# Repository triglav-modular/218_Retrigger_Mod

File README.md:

# 218r Retrigger Mod

This is a small add-on PCB that allows for new triggers to be sent from the 218r on each consecutive note without lifting a finger.  It converts the changes in the v/oct output into triggers and adds them to the pulse output. 

There's no need to change any components on the 218r. The "key" and "pulse" inputs just go to the pads above their respective banana jacks. "out" goes directly to the pulse out bananas.
Use a bolt standoff to install it above the STM32.

https://user-images.githubusercontent.com/3920717/165109417-bb7ef8a8-ca0e-416d-88e8-91f72d75c058.mp4

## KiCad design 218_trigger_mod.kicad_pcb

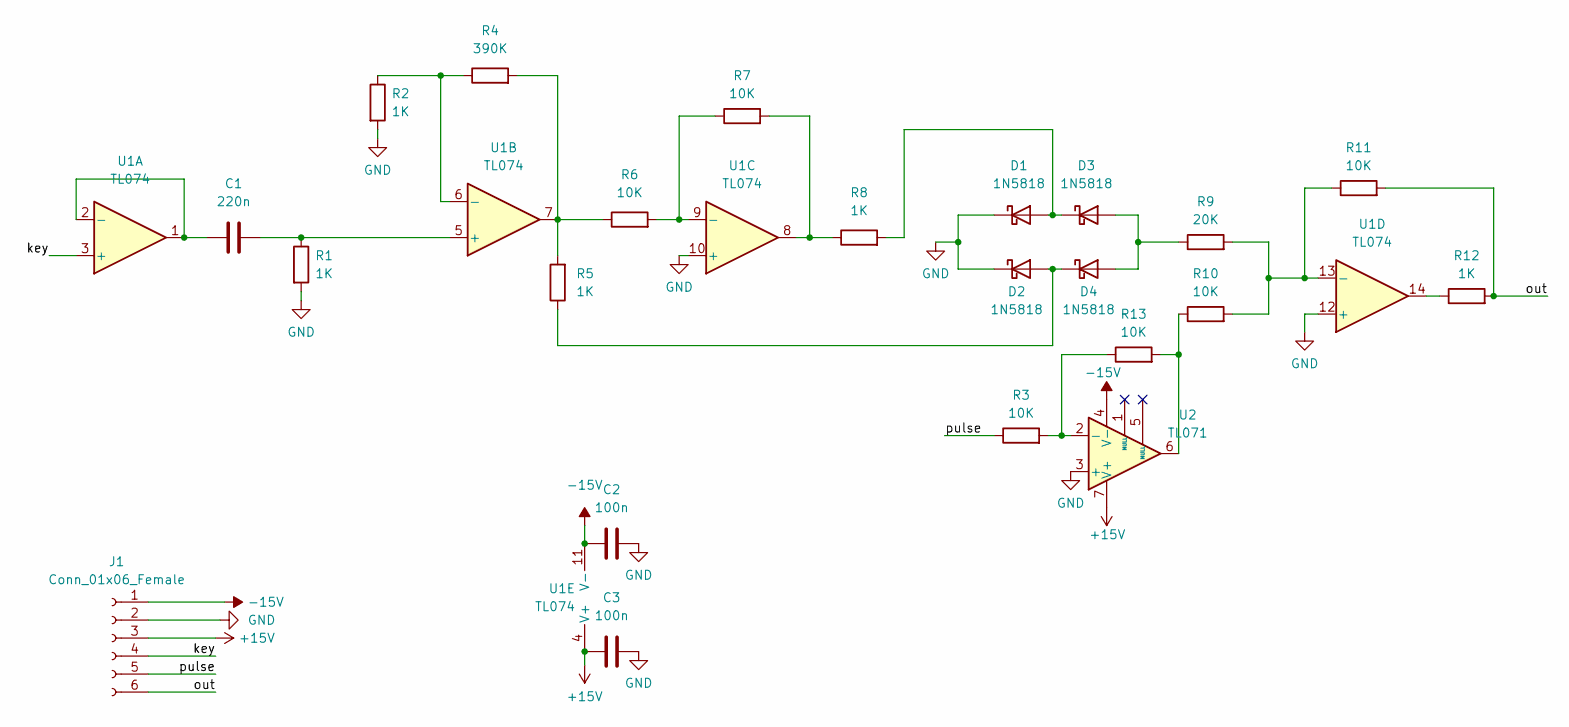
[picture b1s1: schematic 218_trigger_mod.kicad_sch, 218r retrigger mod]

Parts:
C1: 220n; C_Rect_L7.0mm_W3.5mm_P5.00mm
C2, C3: 100n; C_Rect_L7.0mm_W3.5mm_P5.00mm
D1, D2, D3, D4: 1N5818; D_DO-41_SOD81_P7.62mm_Horizontal
J1: Conn_01x06_Female; PinHeader_1x06_P2.54mm_Vertical
R1, R2, R5, R8, R12: 1K; MusicThingModular-10MM_RESISTOR
R3, R6, R7, R10, R11, R13: 10K; MusicThingModular-10MM_RESISTOR
R4: 390K; MusicThingModular-10MM_RESISTOR
R9: 20K; MusicThingModular-10MM_RESISTOR
U1: TL074; DIP-14_W7.62mm
U2: TL071; DIP-8_W7.62mm

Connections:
+15V: C3.1, J1.3, U1.4 (V+), U2.7 (V+)
-15V: C2.1, J1.1, U1.11 (V-), U2.4 (V-)
/key: J1.4, U1.3 (+)
/out: J1.6, R11.2, R12.2
/pulse: J1.5, R3.1
GND: C2.2, C3.2, D1.1 (K), D2.1 (K), J1.2, R1.2, R2.2, U1.10 (+), U1.12 (+), U2.3 (+)
unnamed: C1.1, U1.1, U1.2 (-)
unnamed: C1.2, R1.1, U1.5 (+)
unnamed: D1.2 (A), D3.1 (K), R8.2
unnamed: D2.2 (A), D4.1 (K), R5.1
unnamed: D3.2 (A), D4.2 (A), R9.1
unnamed: R2.1, R4.1, U1.6 (-)
unnamed: R4.2, R5.2, R6.1, U1.7
unnamed: R6.2, R7.1, U1.9 (-)
unnamed: R7.2, R8.1, U1.8
unnamed: R10.1, R13.2, U2.6
unnamed: R9.2, R10.2, R11.1, U1.13 (-)
unnamed: R12.1, U1.14
unnamed: R3.2, R13.1, U2.2 (-)

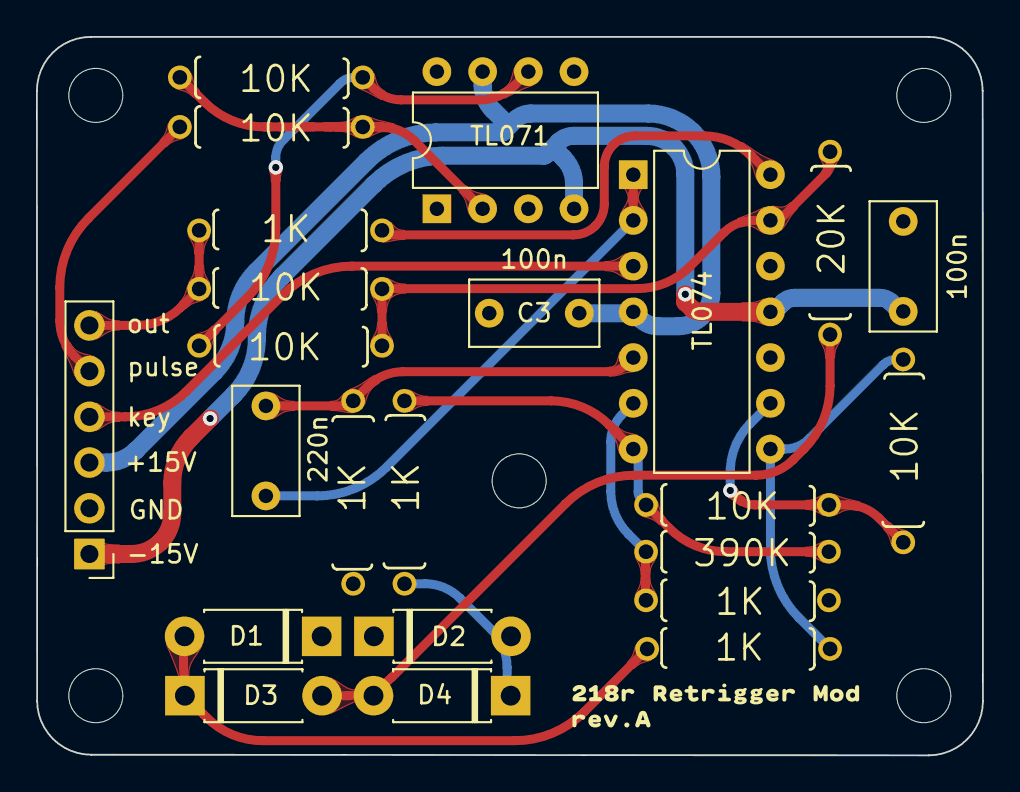
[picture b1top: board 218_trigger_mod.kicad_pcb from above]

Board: 2 copper layers, 52.6 x 39.9 mm, 25 parts (0 on the bottom side), 19 nets.

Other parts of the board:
kibuzzard-62811A1C: G***; kibuzzard-62811A1C
kibuzzard-62811A51: G***; kibuzzard-62811A51

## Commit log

2022-04-22 gitignore
